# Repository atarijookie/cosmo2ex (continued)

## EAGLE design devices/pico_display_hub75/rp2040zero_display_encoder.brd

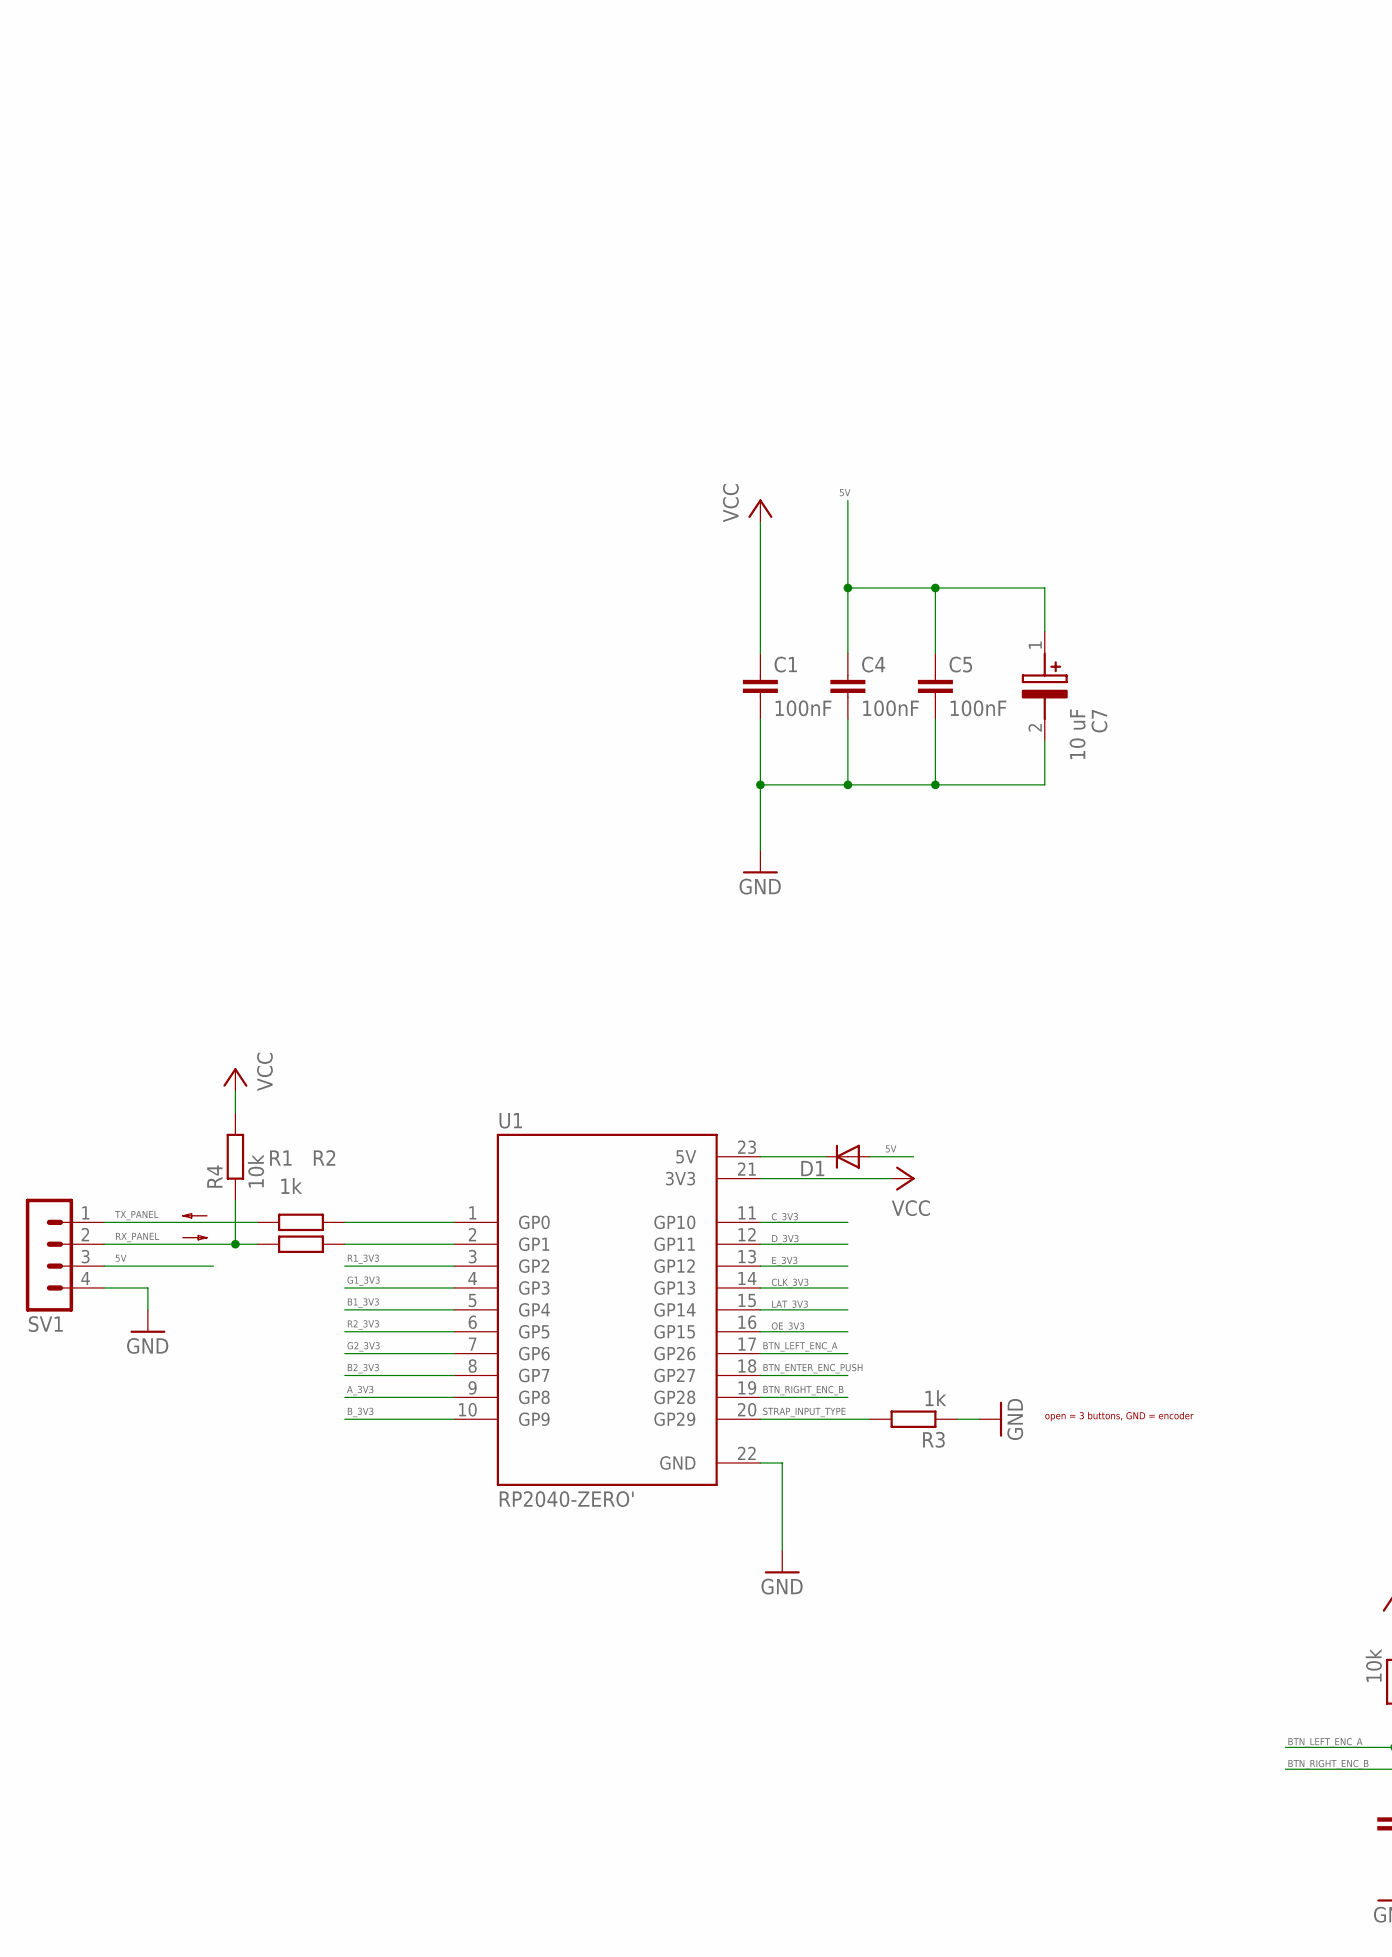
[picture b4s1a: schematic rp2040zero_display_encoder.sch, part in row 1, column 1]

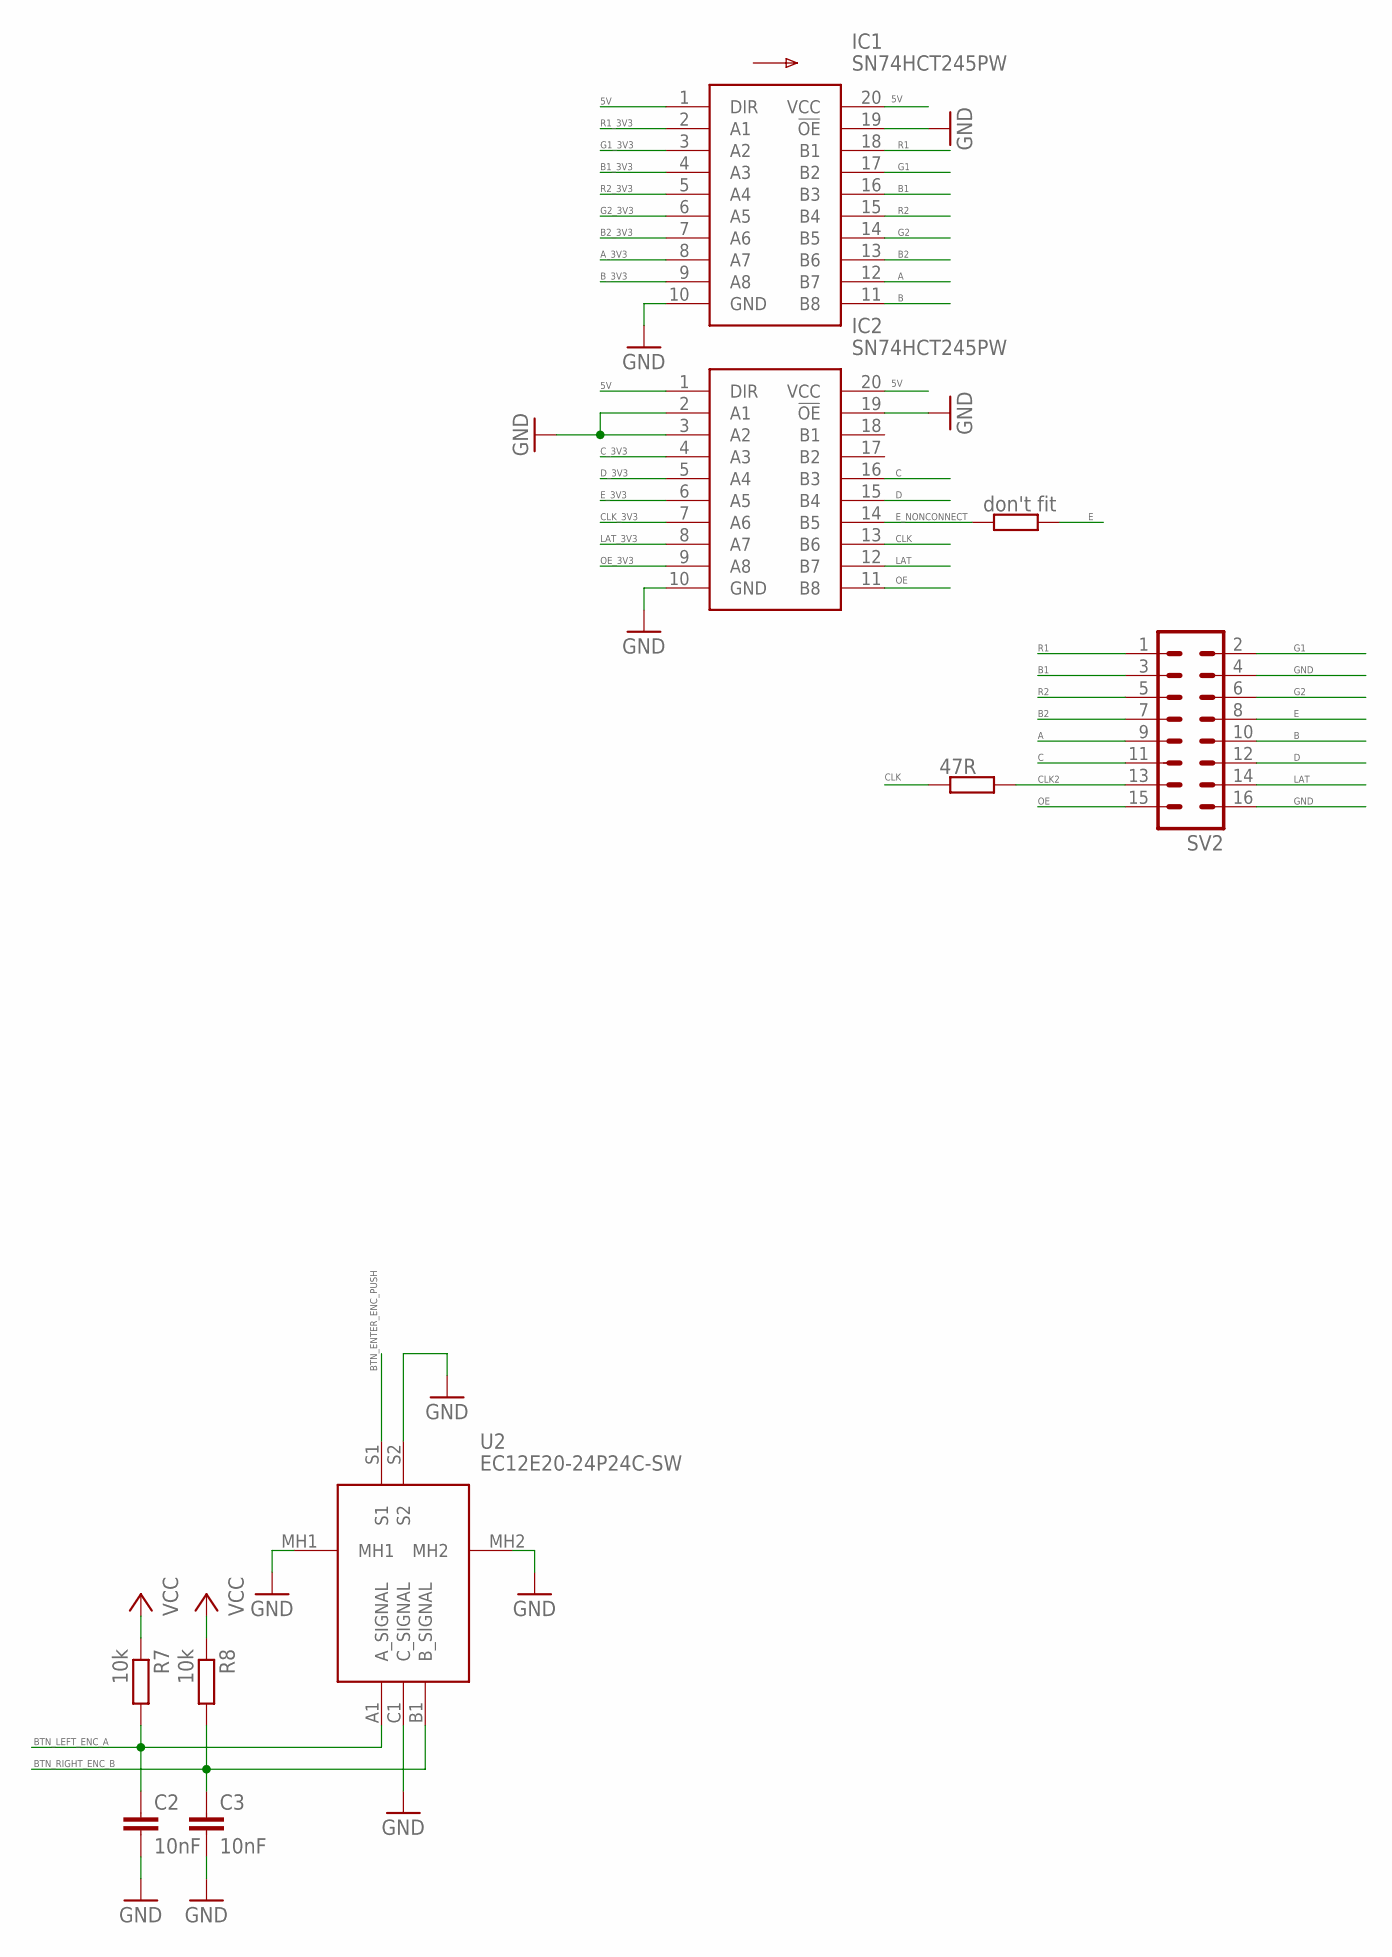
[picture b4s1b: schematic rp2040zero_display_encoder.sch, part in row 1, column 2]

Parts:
C1, C4, C5: 100nF; C0603
C2, C3: 10nF; C0603
C7: 10 uF; CAPPM3528X210N
D1: SK110-DIO; DO214AC
IC1, IC2: SN74HCT245PW; SOP65P640X120-20N
R1, R2, R3: 1k; R0603
R4, R7, R8: 10k; R0603
R5: don't fit; R0603
R6: 47R; R0603
SV1: MA04-1
SV2: ML16
U1: RP2040-ZERO'; MODULE_RP2040-ZERO
U2: EC12E20-24P24C-SW; EC12E2024P24CSW

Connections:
5V: C4.1, C5.1, C7.1 (+), D1.A, IC1.1 (DIR), IC1.20 (VCC), IC2.1 (DIR), IC2.20 (VCC), SV1.3
A: IC1.12 (B7), SV2.9
A_3V3: IC1.8 (A7), U1.9 (GP8)
B: IC1.11 (B8), SV2.10
B1: IC1.16 (B3), SV2.3
B1_3V3: IC1.4 (A3), U1.5 (GP4)
B2: IC1.13 (B6), SV2.7
B2_3V3: IC1.7 (A6), U1.8 (GP7)
BTN_ENTER_ENC_PUSH: U1.18 (GP27), U2.S1
BTN_LEFT_ENC_A: C2.1, R7.2, U1.17 (GP26), U2.A1 (A_SIGNAL)
BTN_RIGHT_ENC_B: C3.1, R8.2, U1.19 (GP28), U2.B1 (B_SIGNAL)
B_3V3: IC1.9 (A8), U1.10 (GP9)
C: IC2.16 (B3), SV2.11
CLK: IC2.13 (B6), R6.1
CLK2: R6.2, SV2.13
CLK_3V3: IC2.7 (A6), U1.14 (GP13)
C_3V3: IC2.4 (A3), U1.11 (GP10)
D: IC2.15 (B4), SV2.12
D_3V3: IC2.5 (A4), U1.12 (GP11)
E: R5.2, SV2.8
E_3V3: IC2.6 (A5), U1.13 (GP12)
E_NONCONNECT: IC2.14 (B5), R5.1
G1: IC1.17 (B2), SV2.2
G1_3V3: IC1.3 (A2), U1.4 (GP3)
G2: IC1.14 (B5), SV2.6
G2_3V3: IC1.6 (A5), U1.7 (GP6)
GND: C1.2, C2.2, C3.2, C4.2, C5.2, C7.2 (-), IC1.10 (GND), IC1.19 (!OE), IC2.2 (A1), IC2.3 (A2), IC2.10 (GND), IC2.19 (!OE), R3.1, SV1.4, SV2.4, SV2.16, U1.22 (GND), U2.C1 (C_SIGNAL), U2.MH1, U2.MH2, U2.S2
LAT: IC2.12 (B7), SV2.14
LAT_3V3: IC2.8 (A7), U1.15 (GP14)
unnamed: R1.2, U1.1 (GP0)
unnamed: R2.2, U1.2 (GP1)
unnamed: D1.C, U1.23 (5V)
OE: IC2.11 (B8), SV2.15
OE_3V3: IC2.9 (A8), U1.16 (GP15)
R1: IC1.18 (B1), SV2.1
R1_3V3: IC1.2 (A1), U1.3 (GP2)
R2: IC1.15 (B4), SV2.5
R2_3V3: IC1.5 (A4), U1.6 (GP5)
RX_PANEL: R2.1, R4.1, SV1.2
STRAP_INPUT_TYPE: R3.2, U1.20 (GP29)
TX_PANEL: R1.1, SV1.1
VCC: C1.1, R4.2, R7.1, R8.1, U1.21 (3V3)

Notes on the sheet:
open = 3 buttons, GND = encoder

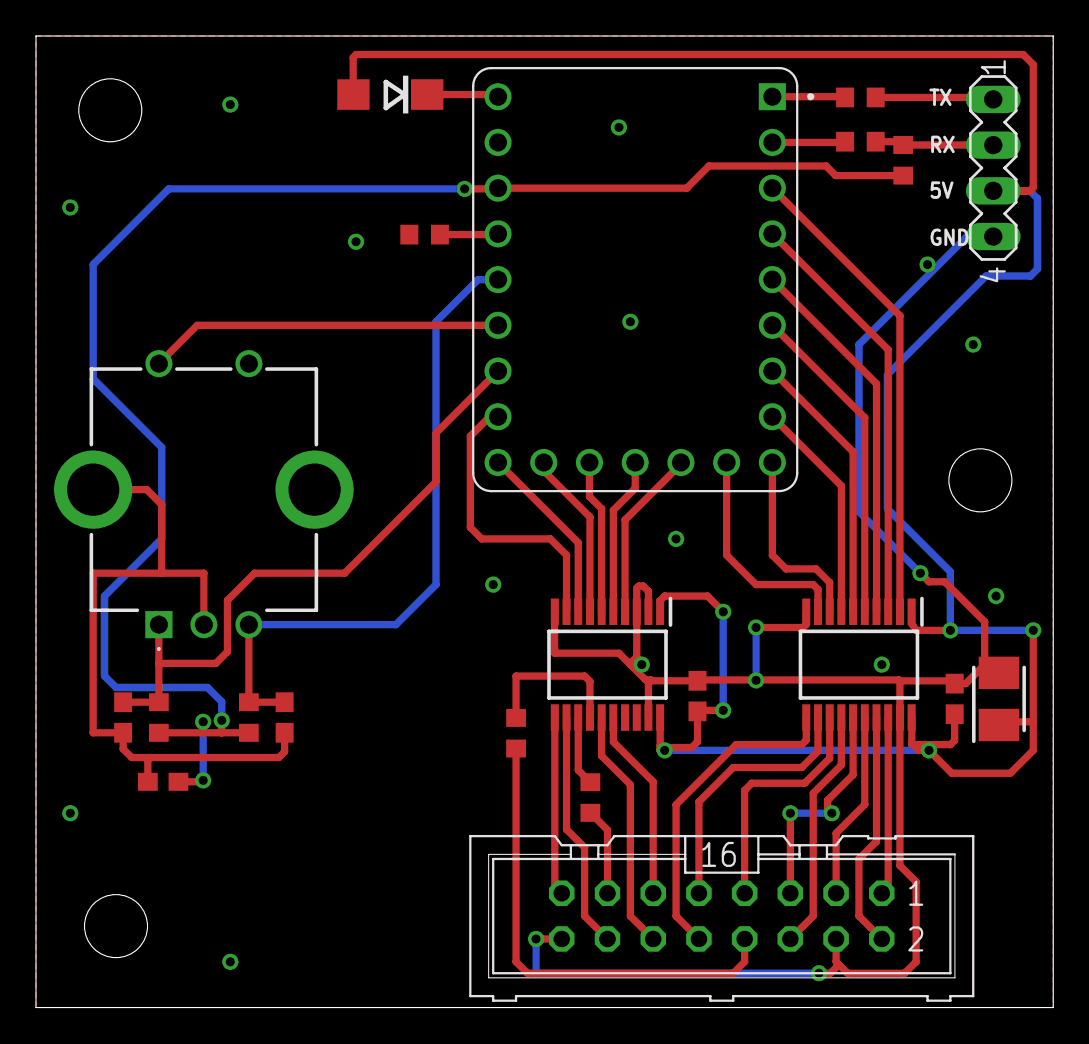
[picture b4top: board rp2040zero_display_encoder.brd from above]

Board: 2 copper layers, 56.5 x 54.0 mm, 21 parts (0 on the bottom side), 42 nets.

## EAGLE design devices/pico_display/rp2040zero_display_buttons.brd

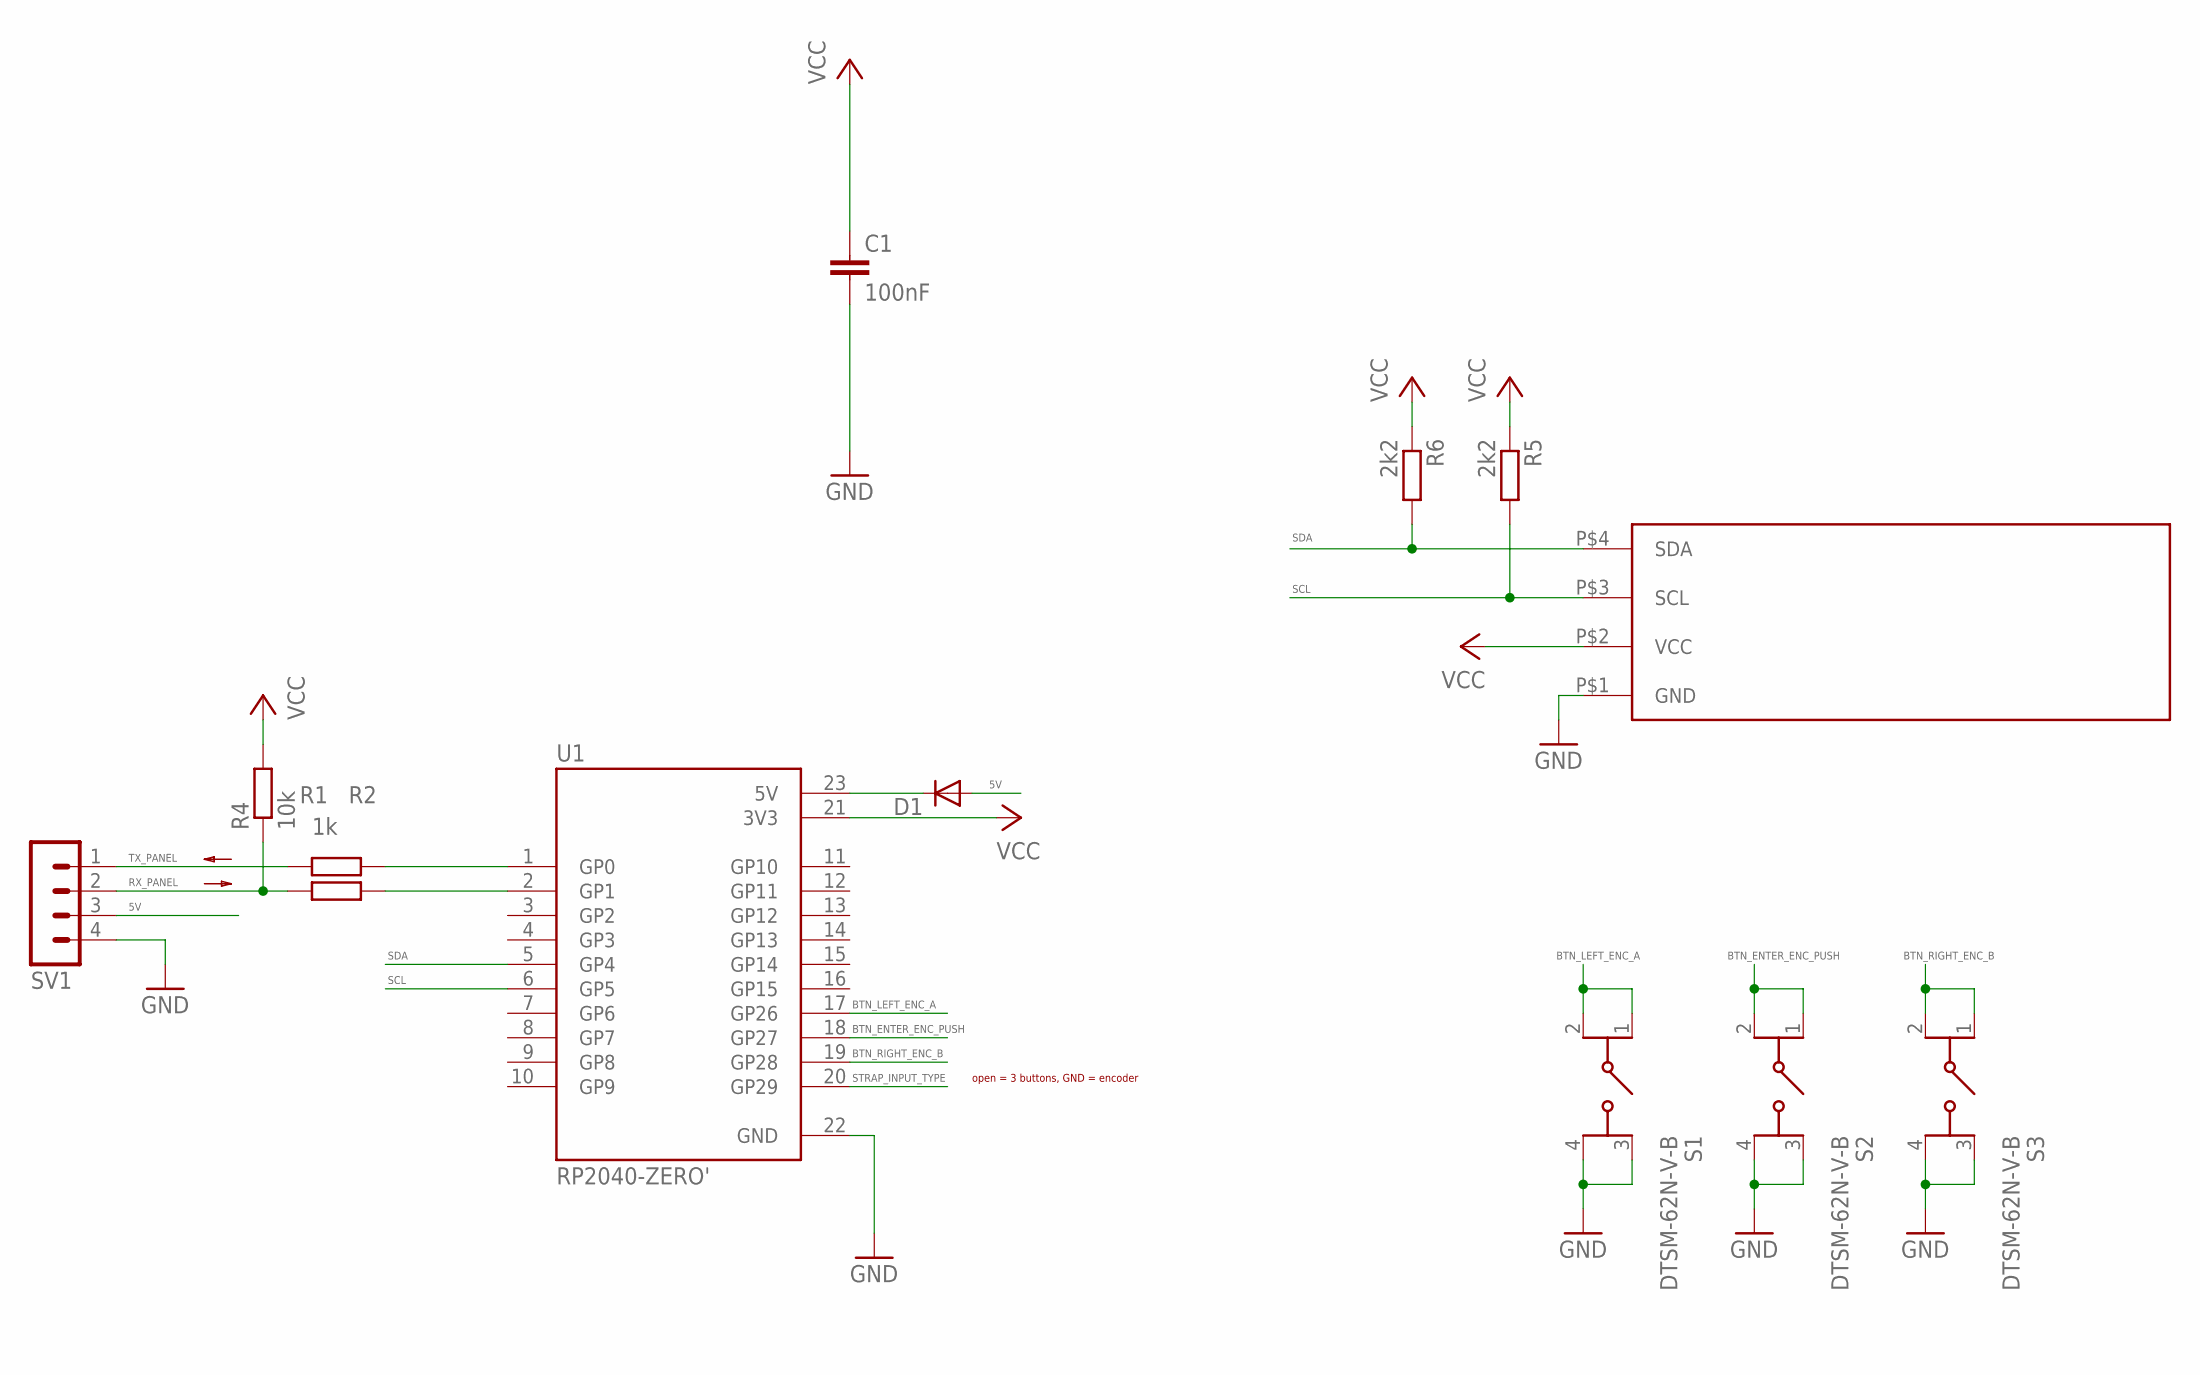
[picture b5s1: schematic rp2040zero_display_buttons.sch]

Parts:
C1: 100nF; C0603
D1: SK110-DIO; DO214AC
R1, R2: 1k; R0603
R4: 10k; R0603
R5, R6: 2k2; R0603
S1, S2, S3: DTSM-62N-V-B; DTSM62NVB
SV1: MA04-1
U1: RP2040-ZERO'; MODULE_RP2040-ZERO
U$1: OLED; SIP

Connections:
5V: D1.A, SV1.3
BTN_ENTER_ENC_PUSH: S2.1 (COM_1), S2.2 (COM_2), U1.18 (GP27)
BTN_LEFT_ENC_A: S1.1 (COM_1), S1.2 (COM_2), U1.17 (GP26)
BTN_RIGHT_ENC_B: S3.1 (COM_1), S3.2 (COM_2), U1.19 (GP28)
GND: C1.2, S1.3 (NO_1), S1.4 (NO_2), S2.3 (NO_1), S2.4 (NO_2), S3.3 (NO_1), S3.4 (NO_2), SV1.4, U1.22 (GND), U$1.P$1 (GND)
unnamed: R1.2, U1.1 (GP0)
unnamed: R2.2, U1.2 (GP1)
unnamed: D1.C, U1.23 (5V)
RX_PANEL: R2.1, R4.1, SV1.2
SCL: R5.2, U1.6 (GP5), U$1.P$3 (SCL)
SDA: R6.2, U1.5 (GP4), U$1.P$4 (SDA)
STRAP_INPUT_TYPE: U1.20 (GP29)
TX_PANEL: R1.1, SV1.1
VCC: C1.1, R4.2, R5.1, R6.1, U1.21 (3V3), U$1.P$2 (VCC)

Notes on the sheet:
open = 3 buttons, GND = encoder

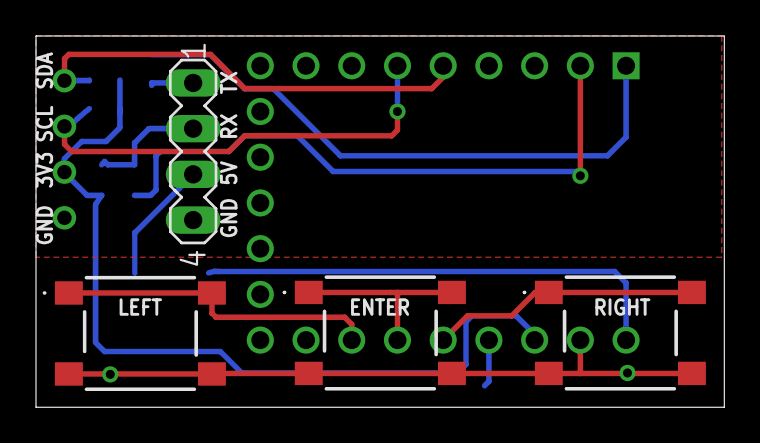
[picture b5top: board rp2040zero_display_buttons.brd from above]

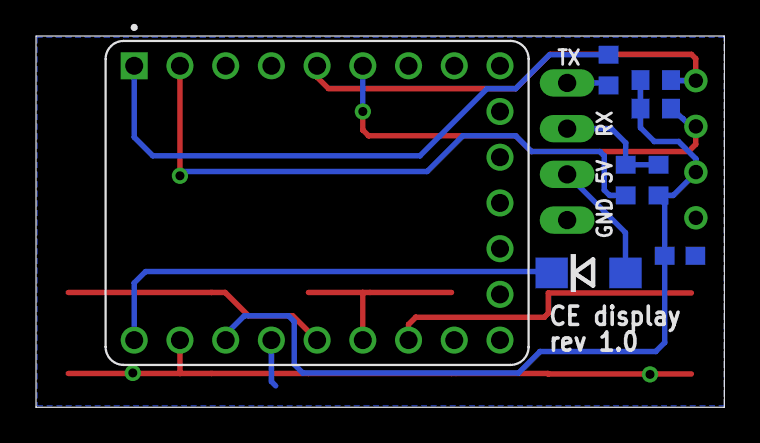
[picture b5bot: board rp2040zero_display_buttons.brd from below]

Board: 2 copper layers, 38.2 x 20.6 mm, 13 parts (8 on the bottom side), 13 nets.

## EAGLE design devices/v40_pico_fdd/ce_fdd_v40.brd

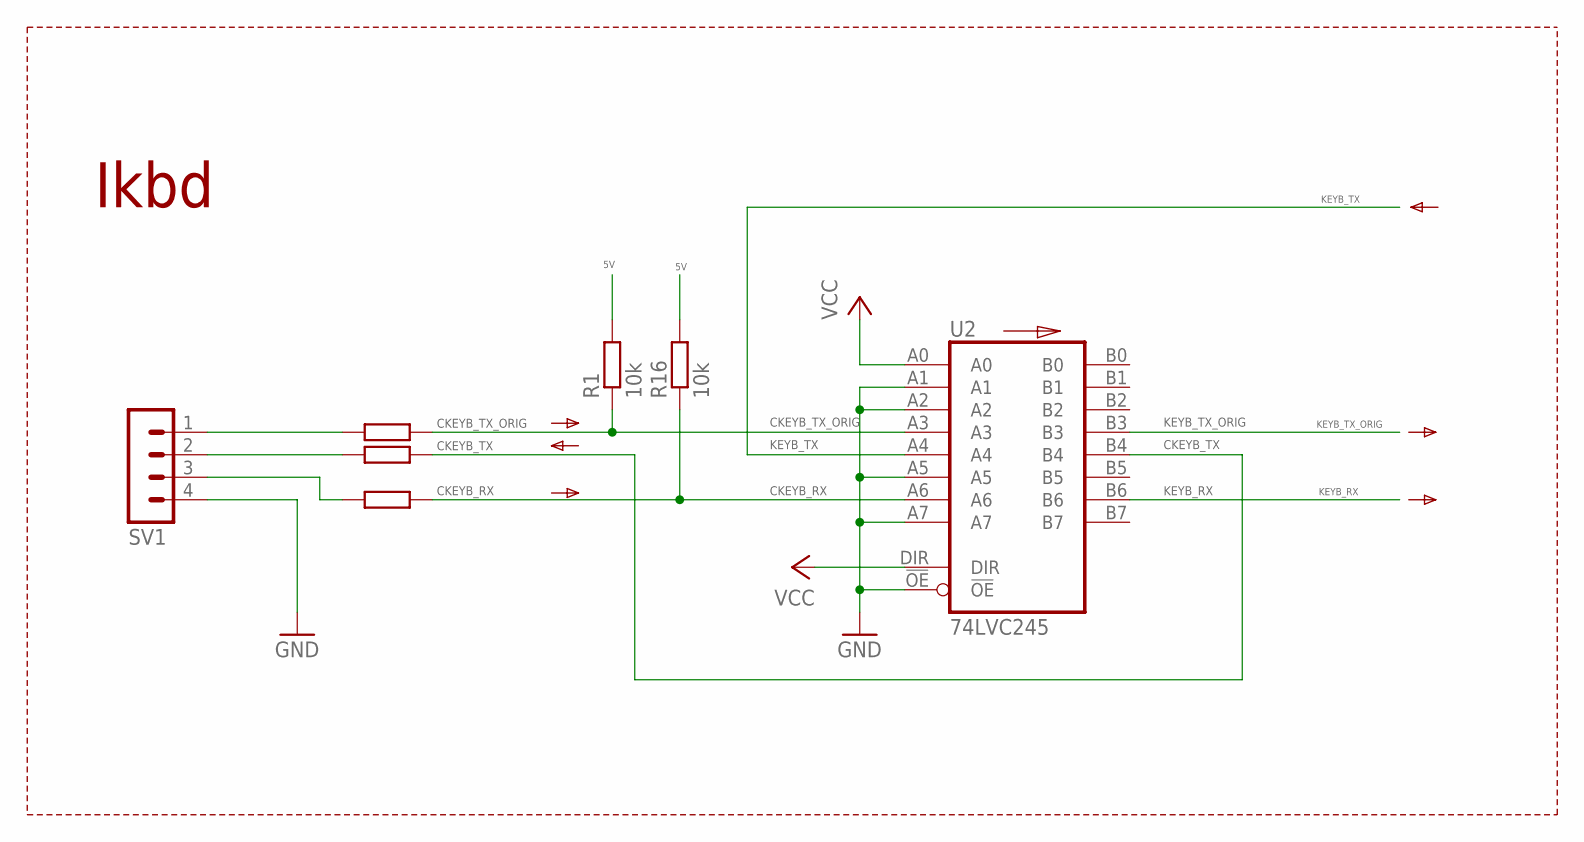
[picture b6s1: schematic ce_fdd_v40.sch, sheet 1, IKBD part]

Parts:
R1, R16: 10k; R0603
R25, R33, R34: 47R; R0603
SV1: MA04-1
U2: 74LVC245; 74LVC245_TSSOP20

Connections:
5V: R1.2, R16.2; also elsewhere on the board
CKEYB_RX: R16.1, R34.1, U2.A6
CKEYB_TX: R33.1, U2.B4
CKEYB_TX_ORIG: R1.1, R25.1, U2.A3
GND: SV1.4, U2.!OE, U2.A1, U2.A2, U2.A5, U2.A7, U2.GND; also elsewhere on the board
KEYB_RX: U2.B6; also elsewhere on the board
KEYB_TX: U2.A4; also elsewhere on the board
KEYB_TX_ORIG: U2.B3; also elsewhere on the board
unnamed: R33.2, SV1.2
VCC: U2.A0, U2.DIR, U2.VCC; also elsewhere on the board
ZKEYB_RX: R34.2, SV1.3
ZKEYB_TX_ORIG: R25.2, SV1.1

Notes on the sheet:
Ikbd

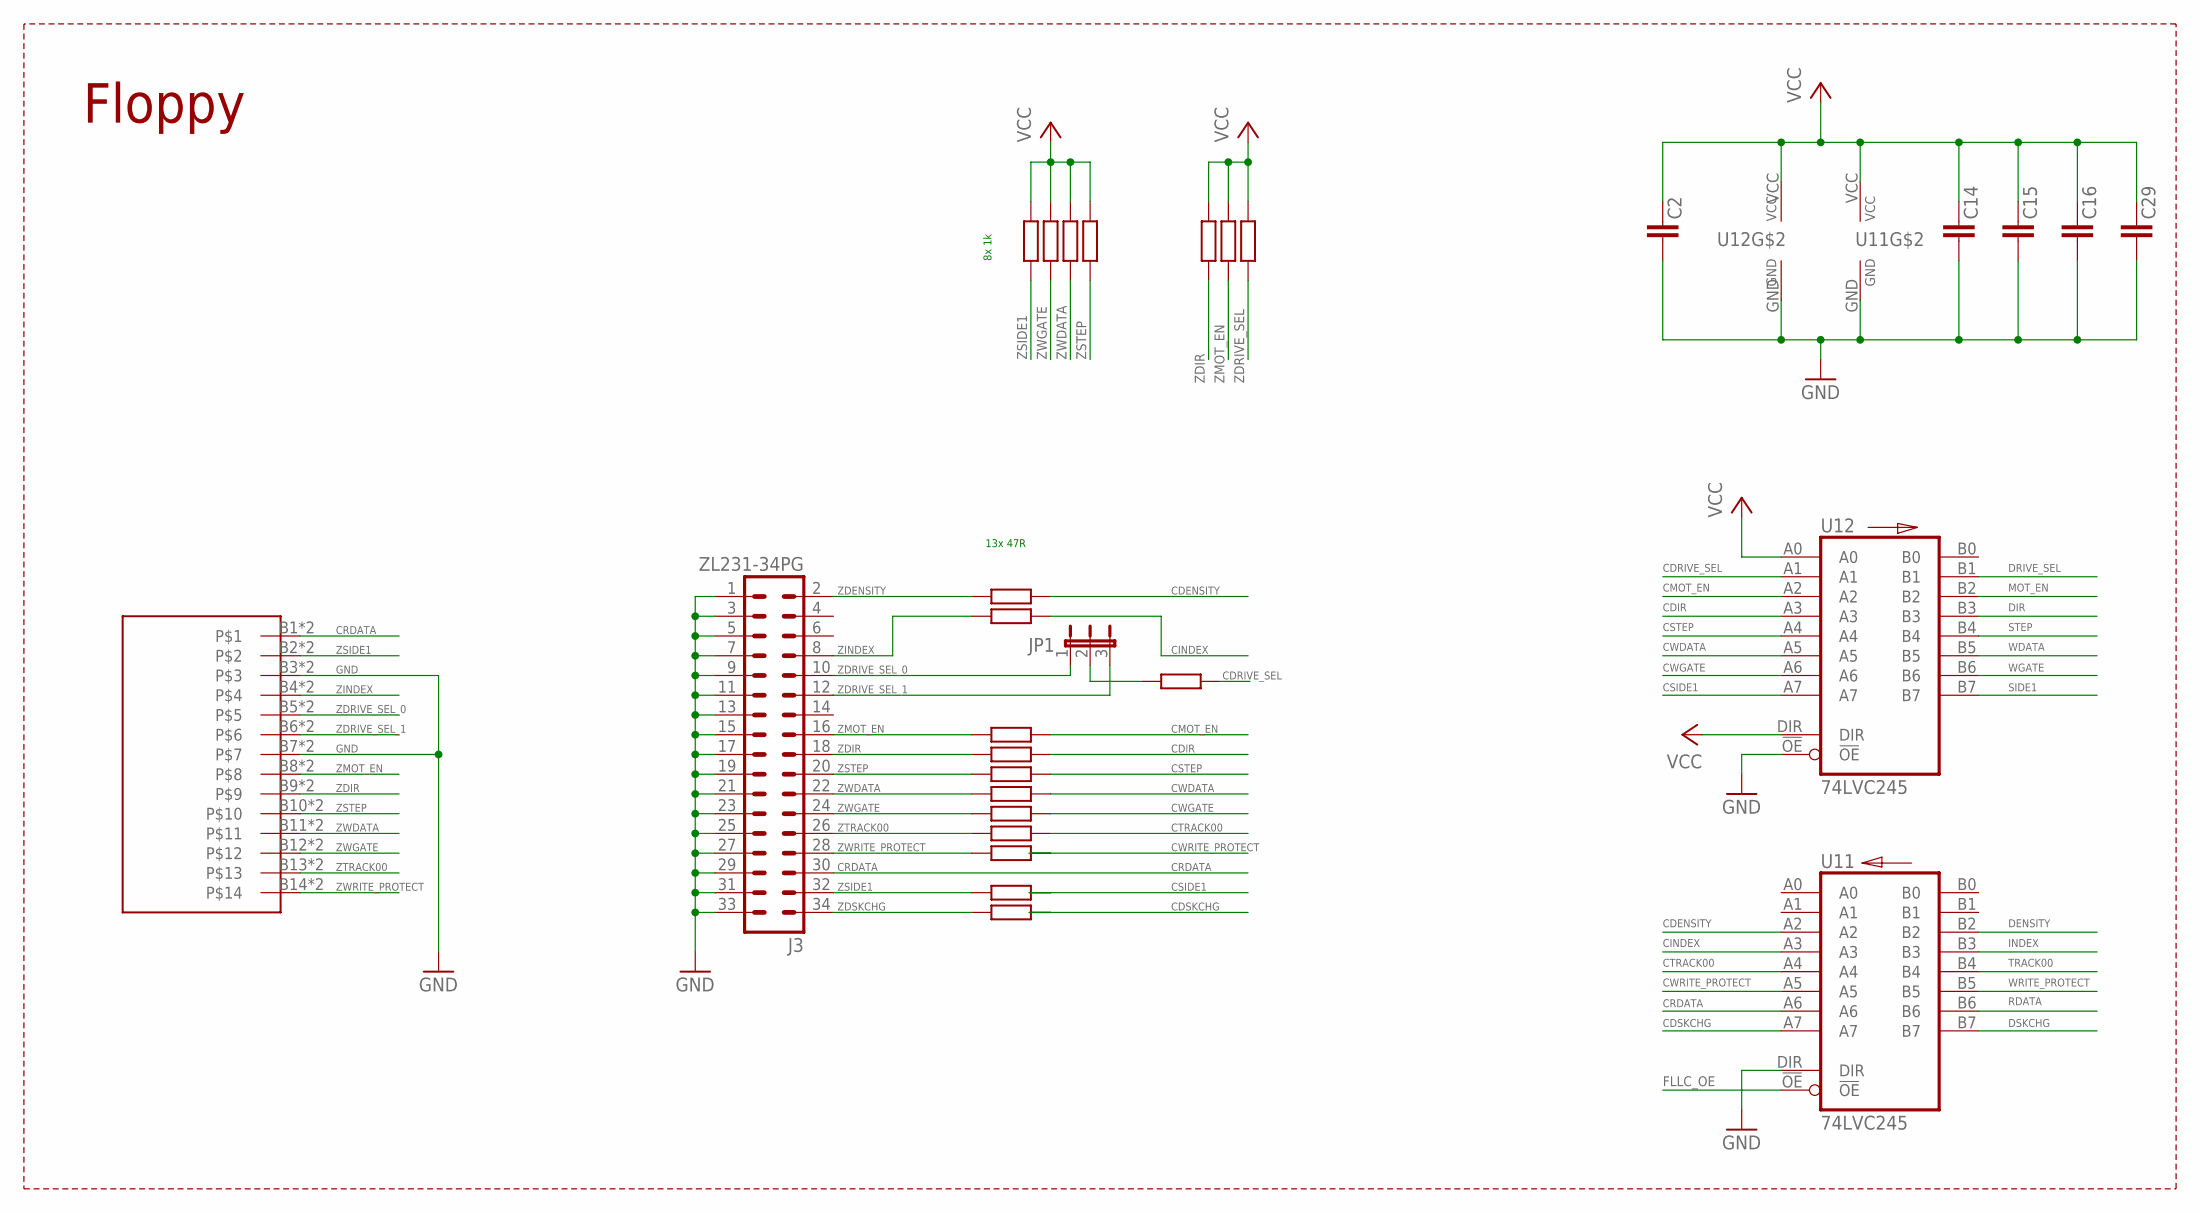
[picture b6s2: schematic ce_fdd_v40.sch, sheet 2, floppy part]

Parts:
C2, C14, C15, C16, C29: 100 nF; C0603
J3: ZL231-34PG; ML34
JP1: JP2E; JP2
R2, R3, R4, R6, R7, R8, R9, R10, R11, R12, R13, R15: 47R; R0603
R22, R23, R24, R26, R27, R28, R29: 1k; R0603
U11, U12: 74LVC245; 74LVC245_TSSOP20
U$1: DIN14

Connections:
CDENSITY: R2.1, U11.A2
CDIR: R7.1, U12.A3
CDRIVE_SEL: R4.1, U12.A1
CDSKCHG: R15.1, U11.A7
CINDEX: R3.1, U11.A3
CMOT_EN: R6.1, U12.A2
CRDATA: J3.30, U11.A6, U$1.B1, U$1.T1
CSIDE1: R13.1, U12.A7
CSTEP: R8.1, U12.A4
CTRACK00: R11.1, U11.A4
CWDATA: R9.1, U12.A5
CWGATE: R10.1, U12.A6
CWRITE_PROTECT: R12.1, U11.A5
DENSITY: U11.B2; also elsewhere on the board
DIR: U12.B3; also elsewhere on the board
DRIVE_SEL: U12.B1; also elsewhere on the board
DSKCHG: U11.B7; also elsewhere on the board
FLLC_OE: U11.!OE; also elsewhere on the board
GND: C2.2, C14.2, C15.2, C16.2, C29.2, J3.1, J3.3, J3.5, J3.7, J3.9, J3.11, J3.13, J3.15, J3.17, J3.19, J3.21, J3.23, J3.25, J3.27, J3.29, J3.31, J3.33, U11.DIR, U11.GND, U12.!OE, U12.GND, U$1.B3, U$1.B7, U$1.T3, U$1.T7; also elsewhere on the board
INDEX: U11.B3; also elsewhere on the board
MOT_EN: U12.B2; also elsewhere on the board
RDATA: U11.B6; also elsewhere on the board
SIDE1: U12.B7; also elsewhere on the board
STEP: U12.B4; also elsewhere on the board
TRACK00: U11.B4; also elsewhere on the board
VCC: C2.1, C14.1, C15.1, C16.1, C29.1, R22.1, R23.1, R24.1, R26.1, R27.1, R28.1, R29.1, U11.VCC, U12.A0, U12.DIR, U12.VCC; also elsewhere on the board
WDATA: U12.B5; also elsewhere on the board
WGATE: U12.B6; also elsewhere on the board
WRITE_PROTECT: U11.B5; also elsewhere on the board
ZDENSITY: J3.2, R2.2
ZDIR: J3.18, R7.2, R27.2, U$1.B9, U$1.T9
ZDRIVE_SEL: JP1.2, R4.2, R29.2
ZDRIVE_SEL_0: J3.10, JP1.1, U$1.B5, U$1.T5
ZDRIVE_SEL_1: J3.12, JP1.3, U$1.B6, U$1.T6
ZDSKCHG: J3.34, R15.2
ZINDEX: J3.8, R3.2, U$1.B4, U$1.T4
ZMOT_EN: J3.16, R6.2, R28.2, U$1.B8, U$1.T8
ZSIDE1: J3.32, R13.2, R22.2, U$1.B2, U$1.T2
ZSTEP: J3.20, R8.2, R26.2, U$1.B10, U$1.T10
ZTRACK00: J3.26, R11.2, U$1.B13, U$1.T13
ZWDATA: J3.22, R9.2, R24.2, U$1.B11, U$1.T11
ZWGATE: J3.24, R10.2, R23.2, U$1.B12, U$1.T12
ZWRITE_PROTECT: J3.28, R12.2, U$1.B14, U$1.T14

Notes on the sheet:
Floppy
13x 47R
8x 1k
